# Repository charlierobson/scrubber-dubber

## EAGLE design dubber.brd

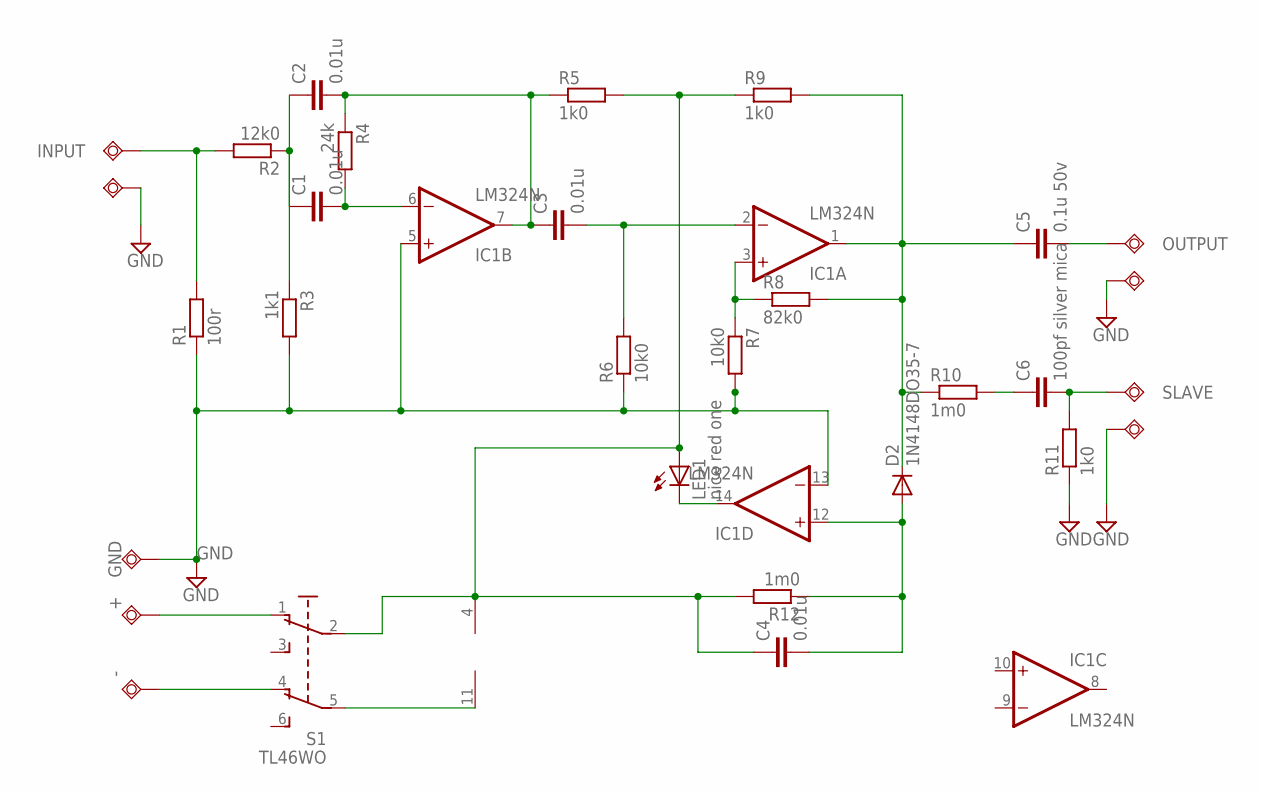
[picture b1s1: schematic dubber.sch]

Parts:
+: TPSQPAD1-13Y; P1-13Y
-: TPSQPAD1-13Y; P1-13Y
C1, C2, C3, C4: 0.01u; C025-025X050
C5: 0.1u 50v; C025-025X050
C6: 100pf silver mica; C025-025X050
D2: 1N4148DO35-7; DO35-7
GND: TPSQPAD1-13Y; P1-13Y
IC1: LM324N; DIL14
INPUT: TPSQPAD1-13Y; P1-13Y
LED1: nice red one; LED5MM
OUTPUT: TPSQPAD1-13Y; P1-13Y
P1-G, P2-G, P3-G: TPSQPAD1-13Y; P1-13Y
R1: 100r; 0207/10
R2: 12k0; 0207/10
R3: 1k1; 0207/10
R4: 24k; 0207/10
R5, R9, R11: 1k0; 0207/10
R6, R7: 10k0; 0207/10
R8: 82k0; 0207/10
R10, R12: 1m0; 0207/10
S1: TL46WO; TL4XWO
SLAVE: TPSQPAD1-13Y; P1-13Y

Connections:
GND: GND.TP, IC1.5 (+IN), IC1.13 (-IN), P1-G.TP, P2-G.TP, P3-G.TP, R1.1, R3.2, R6.1, R7.2, R11.1
unnamed: C1.1, C2.1, R2.1, R3.1
unnamed: C2.2, C3.1, IC1.7 (OUT), R4.1, R5.1
unnamed: C6.1, R10.2
unnamed: +.TP, S1.1 (O)
unnamed: -.TP, S1.4 (O1)
unnamed: C4.2, D2.A, IC1.12 (+IN), R12.1
unnamed: C5.1, D2.C, IC1.1 (OUT), R8.2, R9.2, R10.1
unnamed: IC1.14 (OUT), LED1.K (C)
unnamed: C5.2, OUTPUT.TP
unnamed: C1.2, IC1.6 (-IN), R4.2
unnamed: INPUT.TP, R1.2, R2.2
unnamed: C3.2, IC1.2 (-IN), R6.2
unnamed: IC1.3 (+IN), R7.1, R8.1
unnamed: C6.2, R11.2, SLAVE.TP
V+: C4.1, IC1.4 (V+), LED1.A, R5.2, R9.1, R12.2, S1.2
V-: IC1.11 (V-), S1.5 (P1)

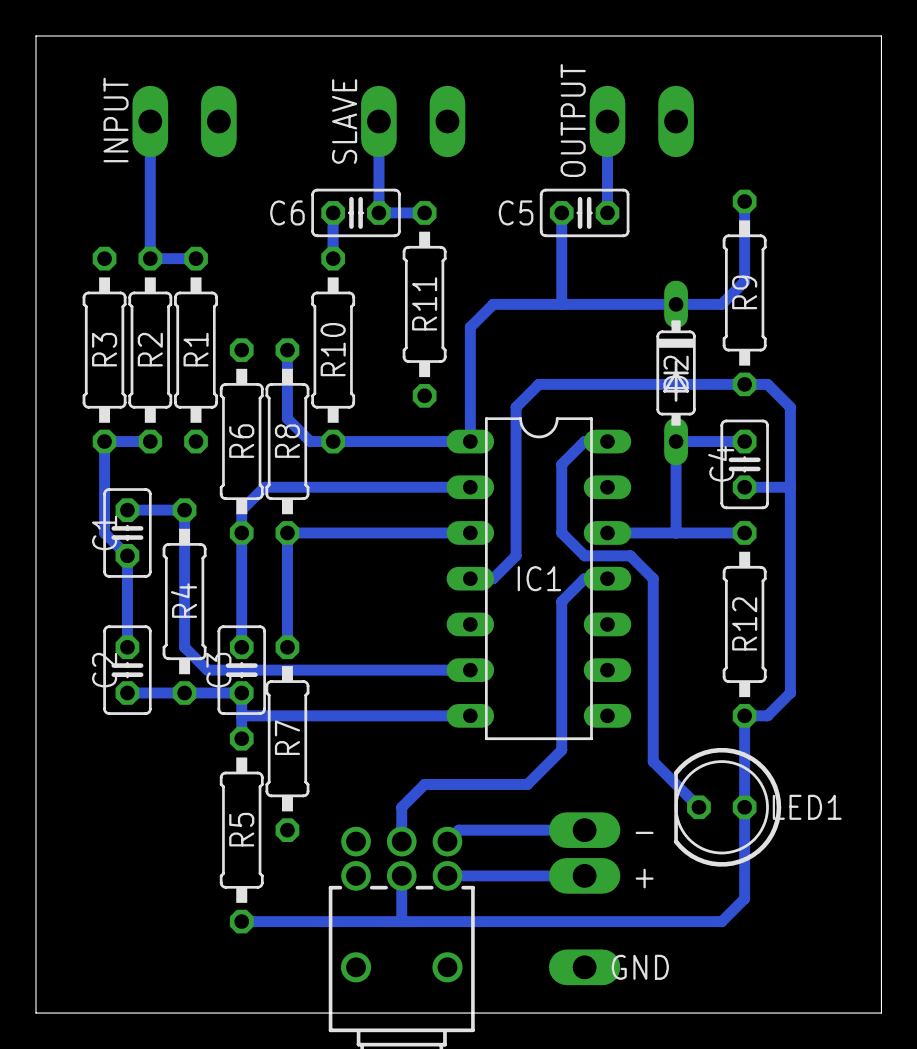
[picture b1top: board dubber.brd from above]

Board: 2 copper layers, 47.0 x 54.3 mm, 31 parts (0 on the bottom side), 17 nets.

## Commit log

2017-10-25 initial layout, before adjusting
2017-10-25 ocd round 1, straighten resistors and miter corners
2017-10-25 ocd round 2, schematic cleanup and moving components into space
2017-10-25 add original images
2017-10-25 tweaks again
